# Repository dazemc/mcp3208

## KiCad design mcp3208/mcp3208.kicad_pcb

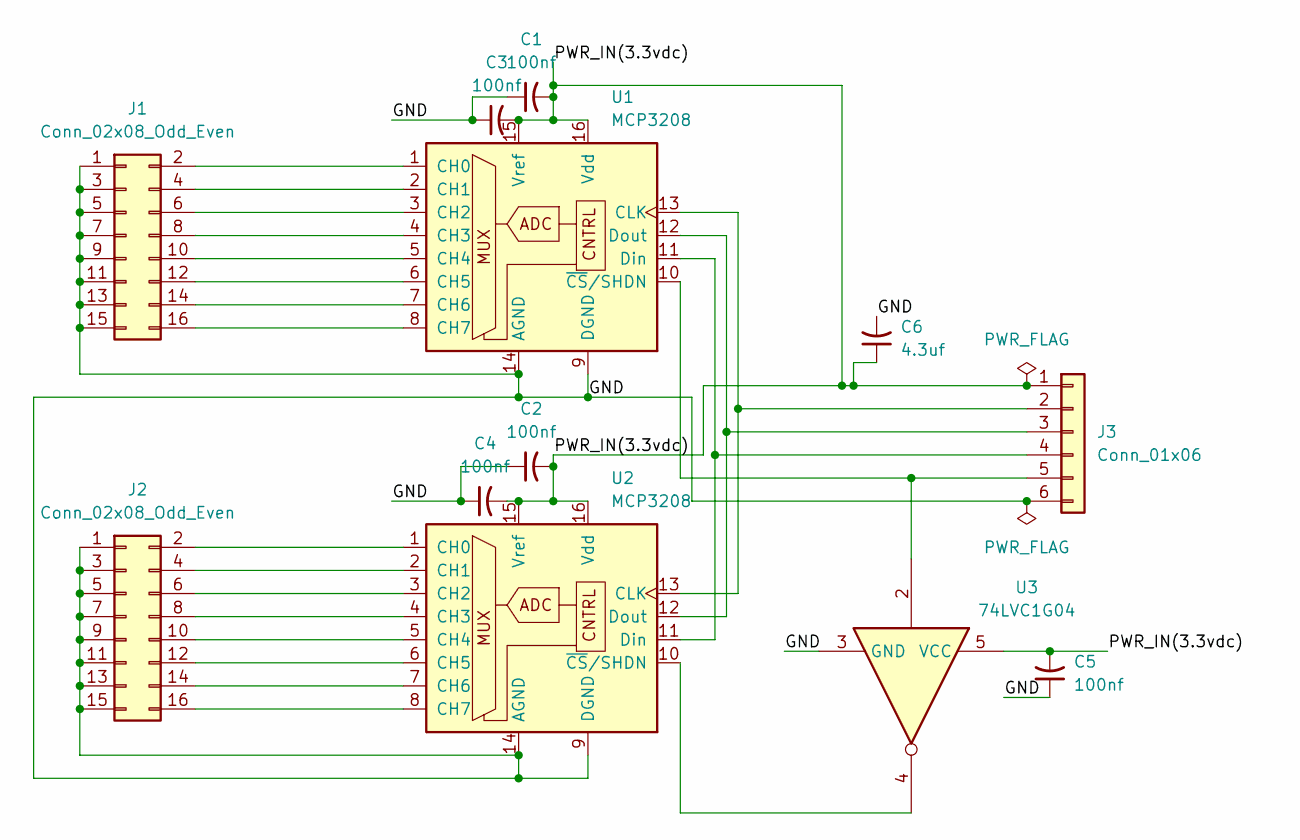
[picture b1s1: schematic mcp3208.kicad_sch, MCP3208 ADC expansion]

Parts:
C1, C2, C3, C4, C5: 100nf; C_0805_2012Metric_Pad1.18x1.45mm_HandSolder
C6: 4.3uf; C_0805_2012Metric_Pad1.18x1.45mm_HandSolder
J1, J2: Conn_02x08_Odd_Even; JST_PHD_B16B-PHDSS_2x08_P2.00mm_Vertical
J3: Conn_01x06; JST_PH_B6B-PH-K_1x06_P2.00mm_Vertical
U1, U2: MCP3208; SOIC-16_3.9x9.9mm_P1.27mm
U3: 74LVC1G04; SOT-353_SC-70-5

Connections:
/GND: C1.1, C2.1, C3.1, C4.1, C5.1, C6.2, J1.1, J1.3, J1.5, J1.7, J1.9, J1.11, J1.13, J1.15, J2.1, J2.3, J2.5, J2.7, J2.9, J2.11, J2.13, J2.15, J3.6, U1.9 (DGND), U1.14 (AGND), U2.9 (DGND), U2.14 (AGND), U3.3 (GND)
/PWR_IN(3.3vdc): C1.2, C2.2, C3.2, C4.2, C5.2, C6.1, J3.1, U1.15 (Vref), U1.16 (Vdd), U2.15 (Vref), U2.16 (Vdd), U3.5 (VCC)
unnamed: J1.2, U1.1 (CH0)
unnamed: J1.4, U1.2 (CH1)
unnamed: J1.6, U1.3 (CH2)
unnamed: J1.8, U1.4 (CH3)
unnamed: J1.10, U1.5 (CH4)
unnamed: J1.12, U1.6 (CH5)
unnamed: J1.14, U1.7 (CH6)
unnamed: J1.16, U1.8 (CH7)
unnamed: J2.2, U2.1 (CH0)
unnamed: J2.4, U2.2 (CH1)
unnamed: J2.6, U2.3 (CH2)
unnamed: J2.8, U2.4 (CH3)
unnamed: J2.10, U2.5 (CH4)
unnamed: J2.12, U2.6 (CH5)
unnamed: J2.14, U2.7 (CH6)
unnamed: J2.16, U2.8 (CH7)
unnamed: J3.2, U1.13 (CLK), U2.13 (CLK)
unnamed: J3.3, U1.12 (Dout), U2.12 (Dout)
unnamed: J3.4, U1.11 (Din), U2.11 (Din)
unnamed: J3.5, U1.10 (~CS/SHDN), U3.2
unnamed: U2.10 (~CS/SHDN), U3.4

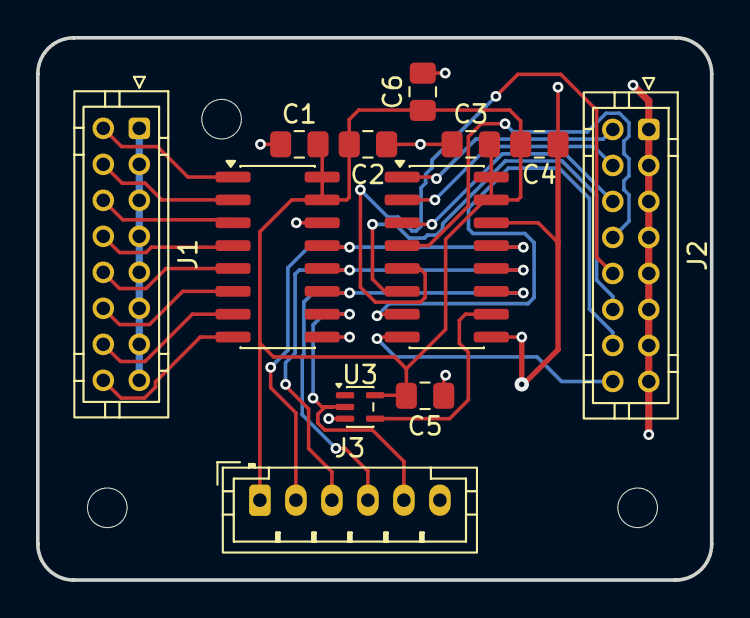
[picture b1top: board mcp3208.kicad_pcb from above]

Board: 2 copper layers, 37.4 x 30.1 mm, 12 parts (0 on the bottom side), 23 nets.
